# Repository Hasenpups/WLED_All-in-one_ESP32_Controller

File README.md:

Shield: [![CC BY-NC-SA 4.0][cc-by-nc-sa-shield]][cc-by-nc-sa]

This work is licensed under a
[Creative Commons Attribution-NonCommercial-ShareAlike 4.0 International License][cc-by-nc-sa].

[![CC BY-NC-SA 4.0][cc-by-nc-sa-image]][cc-by-nc-sa]

[cc-by-nc-sa]: http://creativecommons.org/licenses/by-nc-sa/4.0/
[cc-by-nc-sa-image]: https://licensebuttons.net/l/by-nc-sa/4.0/88x31.png
[cc-by-nc-sa-shield]: https://img.shields.io/badge/License-CC%20BY--NC--SA%204.0-lightgrey.svg

## Donations / Spenden
If somebody wants to support me for upcoming projects :)  
- PayPal:  
- Amazon Giftcard: https://www.amazon.de/Amazon-Gutschein-per-E-Mail-Amazon/dp/B0054PDOV8 - stefan.riese@me.com

# WLED All-in-one ESP32 Controller
This board is designed to connect addressable LEDs/Neopixel strips and handle them with the WLED firmware. Other firmware can be used as well.

## Features
- ESP32-WROOM-32E
- 5,5mm / 2,1mm barrel jack connector for input voltage
- 2 output lines for LED data and LED clock or relais
- level shifter for both outputs (3.3V -> 5V )
- resistor for data line
- support for LED strips with clock signal
- connector to flash firmware with CP2104 (3.3V, TX, RX, GND, IO0, GND)
- :heavy_exclamation_mark: Maximum 5A :heavy_exclamation_mark:
- connector for digital input (3.3V, GND, IO4) (IR remote control for example)
- connector for addon shields (GND, IO32, IO15, IO14, 3.3V, GND, SENSOR_VP)

## BOM
- 1 x WLED All-in-one ESP32 Controller presoldered from https://jlcpcb.com/

|Comment|Designator|Footprint|LCSC
|---|---|---|---
2.7K|R4|R_0603_1608Metric|C13167
100nF|C5,C6,C7|C_0603_1608Metric|C14663
47µF|C3|C_0805_2012Metric|C16780
10µF|C2,C4|C_0603_1608Metric|C19702
330|R5|R_0603_1608Metric|C23138
1000µF|C1|CP_Elec_10x10|C249474
10K|R1,R2,R3|R_0603_1608Metric|C25804
AMS1117-3.3|U1|SOT-89-3|C347256
TXS0102DCU|U3|VSSOP-8_2.3x2mm_P0.5mm|C53434
ESP32-WROOM-32|U2|ESP32-WROOM-32|C701342
LED|D1|LED_0805_2012Metric_Pad1.15x1.40mm_HandSolder|C84256
Barrel_Jack|J2|BarrelJack_Horizontal|
Screw_Terminal_01x04|J3|TerminalBlock_bornier-4_P5.08mm|
Conn_01x03_Female|J4|PinHeader_1x03_P2.54mm_Vertical|
Conn_01x07_Female|J1|PinHeader_1x07_P2.54mm_Vertical|
Conn_01x07_Female|J5|PinHeader_1x07_P2.54mm_Vertical|

- 2 x 2-pin screw terminal (https://www.amazon.de/gp/product/B08JB6SSCJ)
- 1 x Barrel Jack Adapter DS-210 (5,5mm / 2,1mm) (https://www.ebay.de/itm/182379482999)

## Wiring diagram
- https://github.com/Hasenpups/WLED_All-in-one_ESP32_Controller/blob/main/WLED_All-in-one_ESP32_Controller.pdf

## Software
- WLED: https://github.com/Aircoookie/WLED
- Sound reactive WLED: https://github.com/atuline/WLED 

## How to flash software
- Connect IO0 to GND
- Connect USB-UART bridge to 3.3V, TX, RX and GND
    - https://de.aliexpress.com/item/1005002689033373.html
    - https://www.makershop.de/module/kommunikation-module/micro-usb-uart-ttl/
- Open https://install.wled.me/
- Click "Install"
- Select COM port of USB-UART bridge
- Wait until finished

## WLED configuration
- OUT1 - IO16  
- OUT2 - IO17  
- IR receiver - IO18
- Digital microphone (SCK - IO14, WS - IO15, SD - IO32)
- Analog microphone (ADC - SENSOR_VP)
- Button input - IO26

## Addon shields
The following addon shields are available

### Microphone input

- connector for digital and analog microphones 
- INMP401 
- MAX4466 
- MAX9814 

### Prototype area

### Cube builder

- 6 JST-PH connectors to add LED matrix panels to build a cube

## Case
https://www.printables.com/model/373138-wled-all-in-one-esp32-controller-housing

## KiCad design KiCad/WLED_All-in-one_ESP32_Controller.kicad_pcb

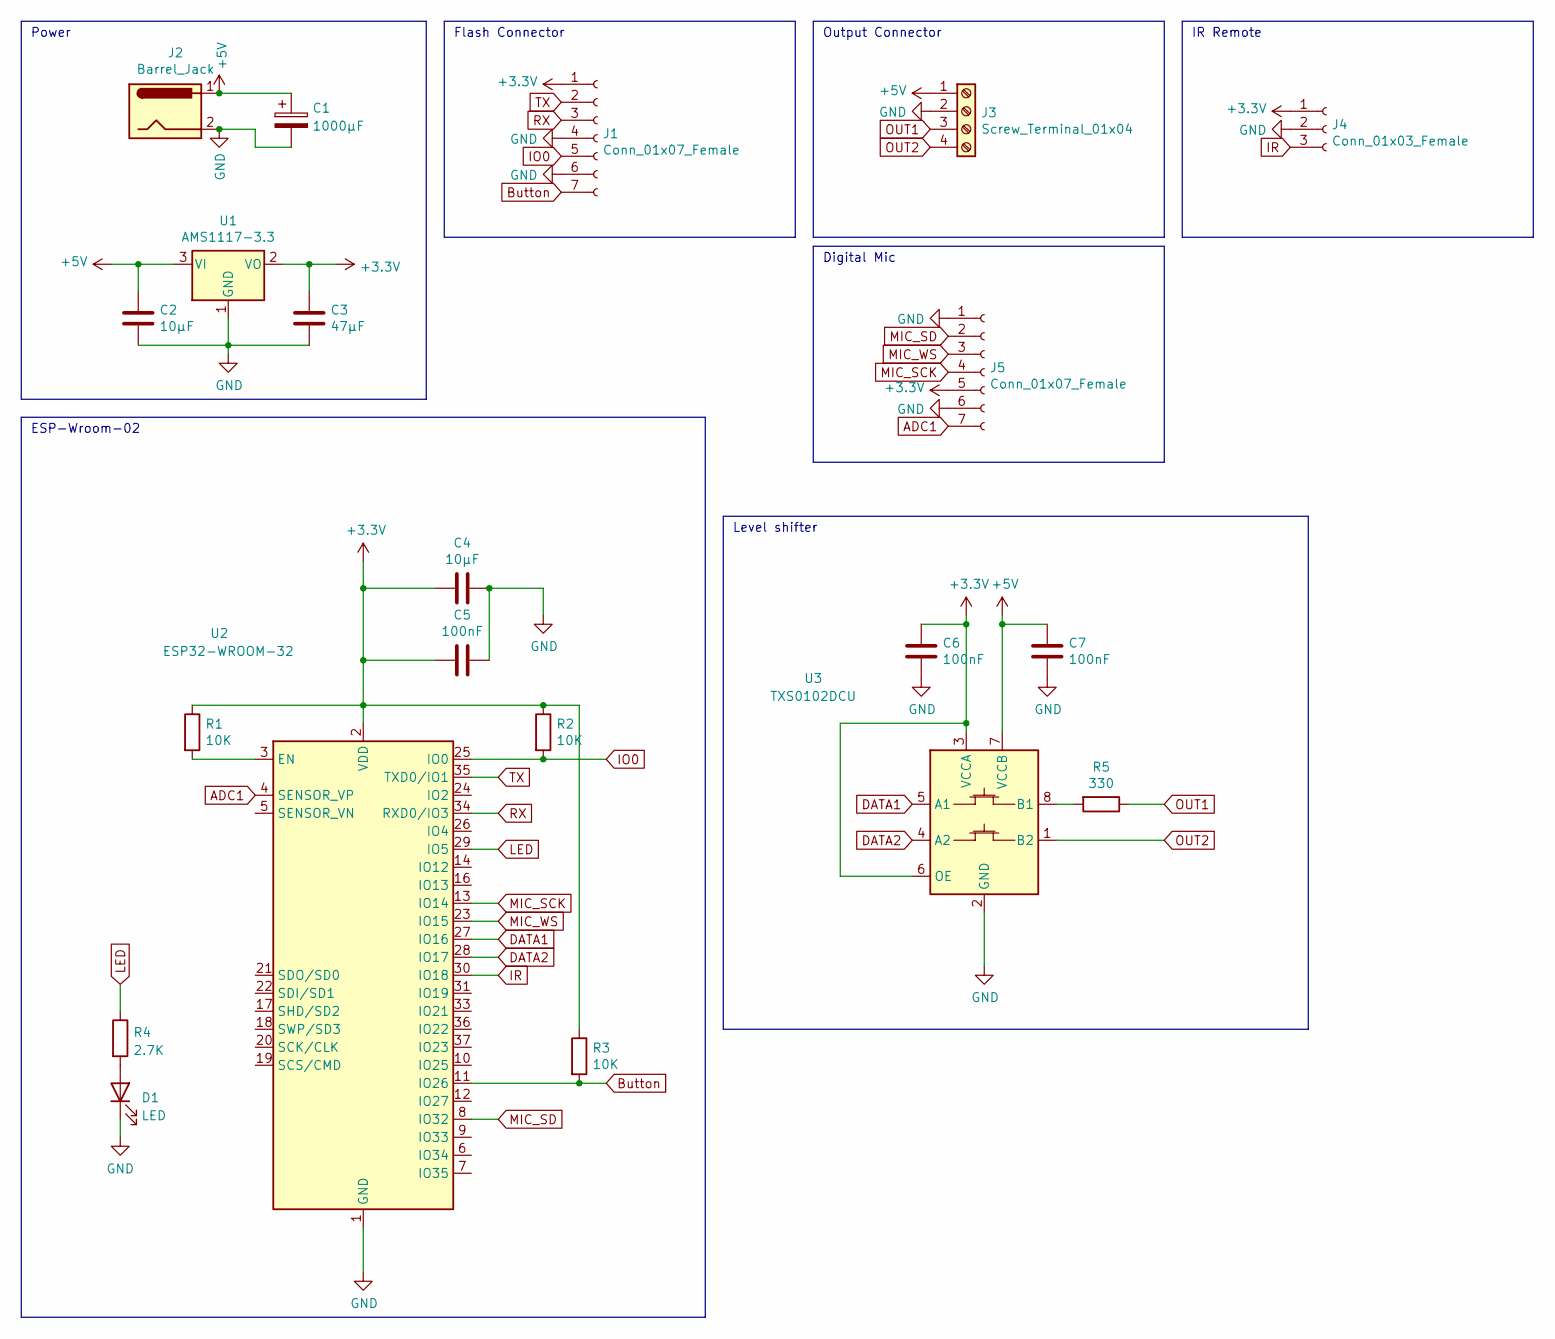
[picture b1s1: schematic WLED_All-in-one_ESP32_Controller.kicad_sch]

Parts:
C1: 1000µF; CP_Elec_10x10
C2, C4: 10µF; C_0603_1608Metric; LCSC C19702
C3: 47µF; C_0805_2012Metric; LCSC C16780
C5: 100nF; C_0603_1608Metric
C6, C7: 100nF; C_0603_1608Metric; LCSC C14663
D1: LED; LED_0805_2012Metric_Pad1.15x1.40mm_HandSolder; LCSC C84256
J1, J5: Conn_01x07_Female; PinHeader_1x07_P2.54mm_Vertical
J2: Barrel_Jack; BarrelJack_Horizontal
J3: Screw_Terminal_01x04; TerminalBlock_bornier-4_P5.08mm
J4: Conn_01x03_Female; PinHeader_1x03_P2.54mm_Vertical
R1, R2: 10K; R_0603_1608Metric; LCSC C25804
R3: 10K; R_0603_1608Metric
R4: 2.7K; R_0603_1608Metric; LCSC C13167
R5: 330; R_0603_1608Metric; LCSC C23138
U1: AMS1117-3.3; SOT-89-3; LCSC C347256
U2: ESP32-WROOM-32
U3: TXS0102DCU; VSSOP-8_2.3x2mm_P0.5mm; LCSC C53434

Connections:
+3V3: C3.1, C4.2, C5.2, C6.1, J1.1, J4.1, J5.5, R1.1, R2.1, R3.1, U1.2 (VO), U2.2 (VDD), U3.3 (VCCA), U3.6 (OE)
+5V: C1.1, C2.1, C7.1, J2.1, J3.1, U1.3 (VI), U3.7 (VCCB)
ADC1: J5.7, U2.4 (SENSOR_VP)
Button: J1.7, R3.2, U2.11 (IO26)
DATA1: U2.27 (IO16), U3.5 (A1)
DATA2: U2.28 (IO17), U3.4 (A2)
GND: C1.2, C2.2, C3.2, C4.1, C5.1, C6.2, C7.2, D1.1 (K), J1.4, J1.6, J2.2, J3.2, J4.2, J5.1, J5.6, U1.1 (GND), U2.1 (GND), U2.15 (GND), U2.38 (GND), U2.39 (GND), U3.2 (GND)
IO0: J1.5, R2.2, U2.25 (IO0)
IR: J4.3, U2.30 (IO18)
LED: R4.1, U2.29 (IO5)
MIC_SCK: J5.4, U2.13 (IO14)
MIC_SD: J5.2, U2.8 (IO32)
MIC_WS: J5.3, U2.23 (IO15)
unnamed: D1.2 (A), R4.2
unnamed: R1.2, U2.3 (EN)
unnamed: R5.2, U3.8 (B1)
OUT1: J3.3, R5.1
OUT2: J3.4, U3.1 (B2)
RX: J1.3, U2.34 (RXD0/IO3)
TX: J1.2, U2.35 (TXD0/IO1)

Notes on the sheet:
Flash Connector
IR Remote
Digital Mic
Power
ESP-Wroom-02
Level shifter
Output Connector

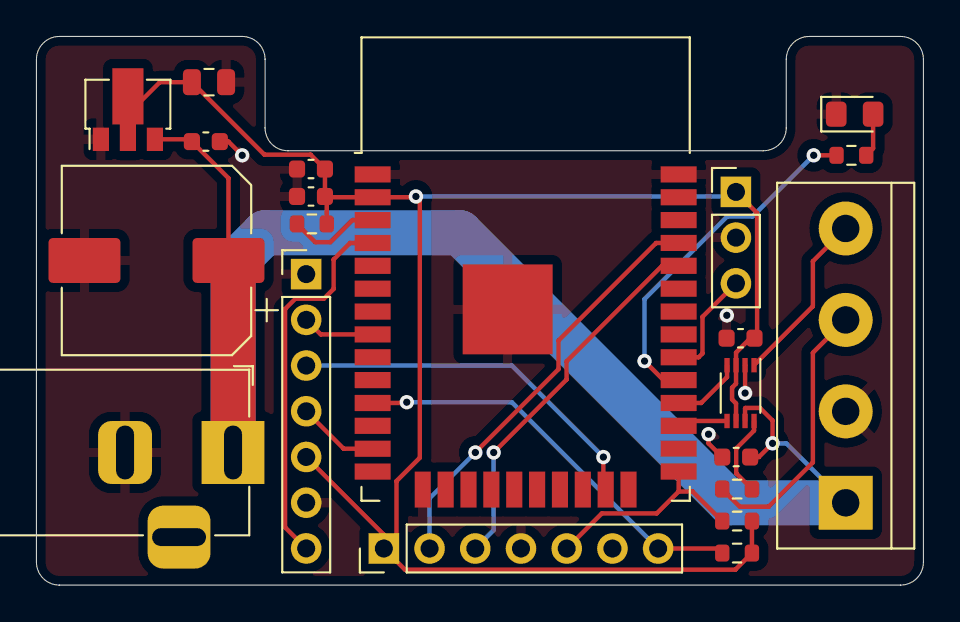
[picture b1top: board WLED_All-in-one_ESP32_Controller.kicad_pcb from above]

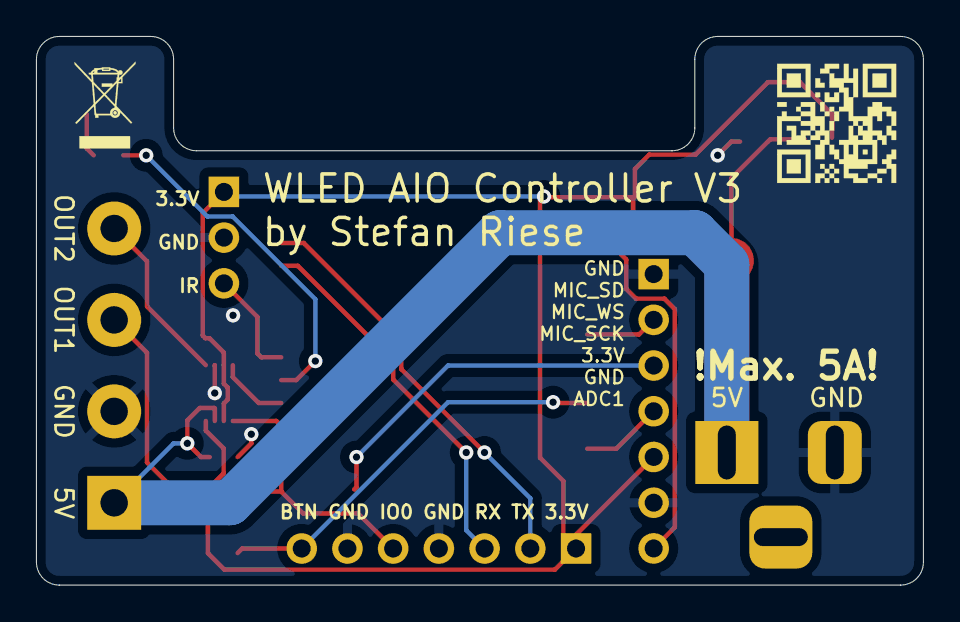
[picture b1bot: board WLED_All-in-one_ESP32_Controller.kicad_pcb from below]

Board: 2 copper layers, 49.3 x 30.5 mm, 23 parts (2 on the bottom side), 20 nets.

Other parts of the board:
G1: LOGO; github_hasenpups_qrcode
G2: LOGO; WEEE_Logo

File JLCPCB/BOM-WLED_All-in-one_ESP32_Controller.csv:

Comment,Designator,Footprint,LCSC
2.7K,R4,R_0603_1608Metric,C13167
100nF,"C5,C6,C7",C_0603_1608Metric,C14663
47µF,C3,C_0805_2012Metric,C16780
10µF,"C2,C4",C_0603_1608Metric,C19702
330,R5,R_0603_1608Metric,C23138
1000µF,C1,CP_Elec_10x10,C249474
10K,"R1,R2,R3",R_0603_1608Metric,C25804
AMS1117-3.3,U1,SOT-89-3,C347256
TXS0102DCU,U3,VSSOP-8_2.3x2mm_P0.5mm,C53434
ESP32-WROOM-32,U2,ESP32-WROOM-32,C701342
LED,D1,LED_0805_2012Metric_Pad1.15x1.40mm_HandSolder,C84256
Barrel_Jack,J2,BarrelJack_Horizontal,
Screw_Terminal_01x04,J3,TerminalBlock_bornier-4_P5.08mm,
Conn_01x03_Female,J4,PinHeader_1x03_P2.54mm_Vertical,
Conn_01x07_Female,J1,PinHeader_1x07_P2.54mm_Vertical,
Conn_01x07_Female,J5,PinHeader_1x07_P2.54mm_Vertical,

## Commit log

2022-06-22 - add micro addon
2022-06-22 add images
2022-06-22 - update images
2022-06-22 - add addons
2023-01-18 - add JLCPCB files
2023-01-18 - add KiCad files
